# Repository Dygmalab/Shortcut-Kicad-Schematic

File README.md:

Shortcut v4 schematic and board layout. This is the version that
[Dygma](http://www.dygma.com) used for conducting closed beta testing of the
shortcut gaming keyboard.

[Schematic PDF](schematic.pdf)

Copyright Dygma 2017.

The firmware for the keyboard is part of the [Kaleidoscope
project](https://github.com/keyboardio/Kaleidoscope). The
specific implementation is defined in the [Shortcut Hardware
Plugin](https://github.com/Dygmalab/Kaleidoscope-Hardware-Shortcut).

This documentation describes Open Hardware and is licensed under the
[CERN OHL v. 1.2.](cern_ohl_v_1_2.txt)

You may redistribute and modify this documentation under the terms of the
CERN OHL v.1.2. (http://ohwr.org/cernohl). This documentation is distributed
WITHOUT ANY EXPRESS OR IMPLIED WARRANTY, INCLUDING OF
MERCHANTABILITY, SATISFACTORY QUALITY AND FITNESS FOR A
PARTICULAR PURPOSE. Please see the CERN OHL v.1.2 for applicable
conditions

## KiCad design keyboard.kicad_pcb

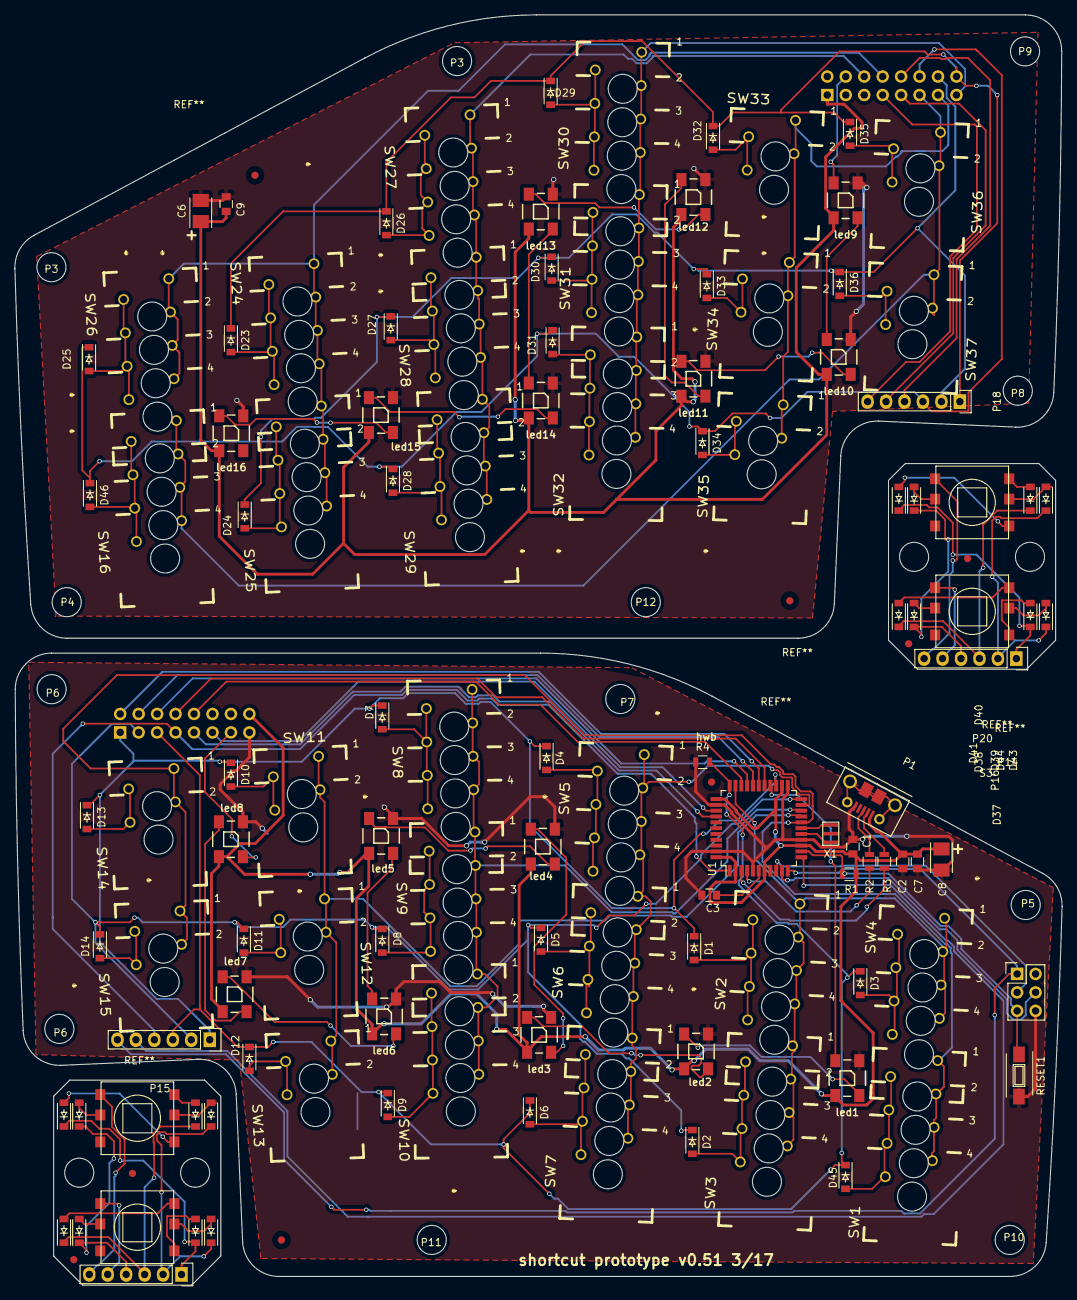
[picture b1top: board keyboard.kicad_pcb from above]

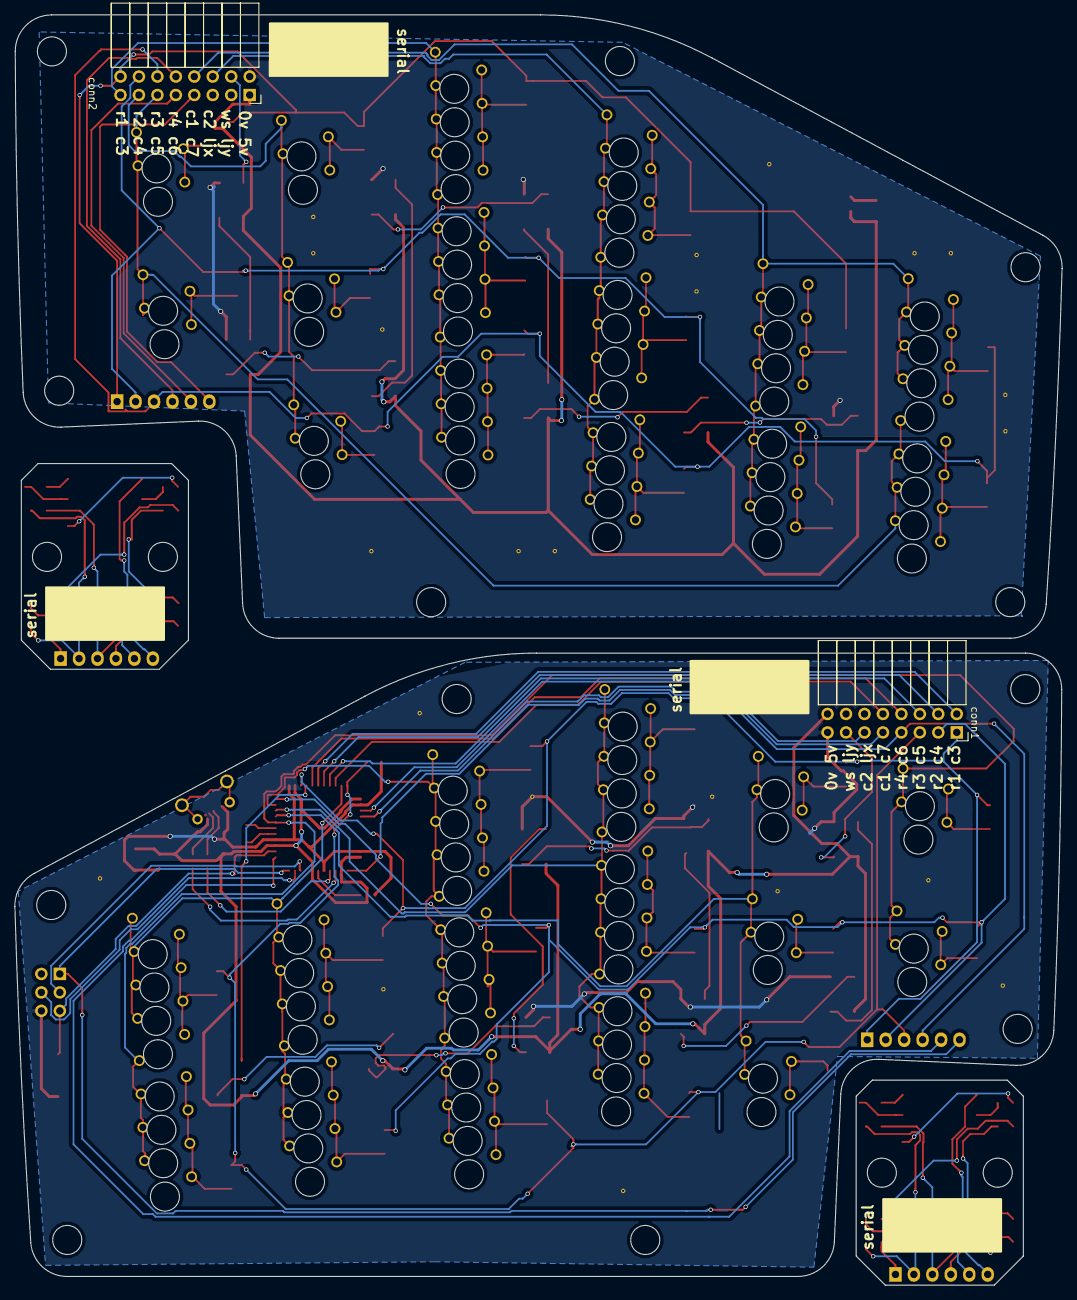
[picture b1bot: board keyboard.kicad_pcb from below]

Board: 2 copper layers, 144.1 x 174.8 mm, 134 parts (2 on the bottom side), 102 nets.

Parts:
C1, C3: 1u; C_0805
C2, C7, C9: 0.1u; C_0805
C6, C8: 2.2u; TantalC_SizeB_EIA-3528_Reflow
D1, D2, D3, D4, D5, D6, D7, D8, D9, D10, D11, D12, D13, D14, D15, D16, D17, D18, D19, D20, D21, D22, D23, D24, D25, D26, D27, D28, D29, D30, D31, D32, D33, D34, D35, D36, D37, D38, D39, D40, D41, D42, D43, D44, D45, D46: D; SOD-123
P1: USB_OTG; USB MICRO B
P2: CONN_02X03; Pin_Header_Straight_2x03
P3, P3#2, P4, P5, P6, P6#2, P7, P8, P9, P10, P11, P12, P13, P14, P17, P20: CONN_01X01; MountingHole_4mm
P15, P16, P16#2, P18: CONN_01X06; Pin_Header_Straight_1x06
R1, R4: 10k; R_0805
R2, R3: 22r; R_0805
RESET1: SW_PUSH; SW_SPST_FSMSM
S1, S2, S3, S4: alps_4way; alps 4way smt
SW1, SW2, SW3, SW4, SW5, SW6, SW7, SW8, SW9, SW10, SW16, SW24, SW25, SW26, SW27, SW28, SW29, SW30, SW31, SW32: SW_PUSH; CHERRY_MXx4
SW11, SW12, SW13, SW14, SW15, SW33, SW34, SW35, SW36, SW37: SW_PUSH; CHERRY_MXx2
U1: ATmega32U4; LQFP-44_10x10mm_Pitch0.8mm
X1: CRYSTAL_SMD; cstce-v
conn1, conn2: CONN_02X08; Socket_Strip_Angled_2x08
led1, led2, led3, led4, led5, led6, led7, led8, led9, led10, led11, led12, led13, led14, led15, led16: ws2812b; WS2812B

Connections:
+5V: C1.1, C2.1, C6.1, C7.1, C8.1, C9.1, P1.1, R1.2, U1.2, U1.7, U1.14, U1.24, U1.34, U1.44, conn1.16, conn2.1, led1.1, led2.1, led3.1, led4.1, led5.1, led6.1, led7.1, led8.1, led9.1, led10.1, led11.1, led12.1, led13.1, led14.1, led15.1, led16.1
/col1: U1.37, conn1.9
/col2: U1.36, conn1.11
/col3: U1.28, conn1.2
/col4: U1.29, conn1.4
/col5: U1.30, conn1.6
/col6: U1.27, conn1.8
/col7: U1.31, conn1.10
/col8: SW2.1, SW3.1, SW4.1, U1.32
/col9: SW5.1, SW6.1, SW7.1, U1.21
/col10: SW8.1, SW9.1, SW10.1, U1.20
/col11: SW11.1, SW12.1, SW13.1, U1.19
/col12: SW1.1, SW14.1, SW15.1, U1.18
/col13: P15.5, U1.12
/col14: P2.1, P15.6, U1.11
/l-col1: SW24.1, SW25.1, SW26.1, conn2.8
/l-col2: SW27.1, SW28.1, SW29.1, conn2.6
/l-col3: SW30.1, SW31.1, SW32.1, conn2.15
/l-col4: SW33.1, SW34.1, SW35.1, conn2.13
/l-col5: SW16.1, SW36.1, SW37.1, conn2.11
/l-col6: P18.5, conn2.9
/l-col7: P18.6, conn2.7
/l-row1: D23.1, D26.1, D29.1, D32.1, D35.1, P18.1, conn2.16
/l-row2: D24.1, D27.1, D30.1, D33.1, D36.1, P18.2, conn2.14
/l-row3: D25.1, D28.1, D31.1, D34.1, D46.1, P18.3, conn2.12
/l-row4: P18.4, conn2.10
/l-ws2812-out: conn2.4, led9.4
/mosi: P2.4, U1.10
/reset: P2.5, R1.1, RESET1.1, U1.13
/right keys/thumb/col1: P16.5, P16#2.5, S1.4, S3.4
/right keys/thumb/col2: P16.6, P16#2.6, S2.4, S4.4
/right keys/thumb/row1: D15.1, D19.1, D37.1, D41.1, P16.1, P16#2.1
/right keys/thumb/row2: D16.1, D20.1, D38.1, D42.1, P16.2, P16#2.2
/right keys/thumb/row3: D17.1, D21.1, D39.1, D43.1, P16.3, P16#2.3
/right keys/thumb/row4: D18.1, D22.1, D40.1, D44.1, P16.4, P16#2.4
/row1: D1.1, D4.1, D7.1, D10.1, D13.1, P15.1, U1.25, conn1.1
/row2: D2.1, D5.1, D8.1, D11.1, D14.1, P15.2, U1.22, conn1.3
/row3: D3.1, D6.1, D9.1, D12.1, D45.1, P15.3, R4.2, U1.33, conn1.5
/row4: P15.4, U1.1, conn1.7
/sck: P2.3, U1.9
/ws2812: U1.26, led1.4
/ws2812-out: conn1.13, led8.2
Earth: C1.2, C2.2, C3.2, C6.2, C7.2, C8.2, C9.2, P1.5, P2.6, R4.1, RESET1.2, U1.5, U1.15, U1.23, U1.35, U1.43, X1.3, conn1.15, conn2.2, led1.3, led2.3, led3.3, led4.3, led5.3, led6.3, led7.3, led8.3, led9.3, led10.3, led11.3, led12.3, led13.3, led14.3, led15.3, led16.3
unnamed: C3.1, U1.6
unnamed: D1.2, SW2.2
unnamed: D2.2, SW3.2
unnamed: D3.2, SW4.2
unnamed: D4.2, SW5.2
unnamed: D5.2, SW6.2
unnamed: D6.2, SW7.2
unnamed: D7.2, SW8.2
unnamed: D8.2, SW9.2
unnamed: D9.2, SW10.2
unnamed: D10.2, SW11.2
unnamed: D11.2, SW12.2
unnamed: D12.2, SW13.2
unnamed: D13.2, SW14.2
unnamed: D14.2, SW15.2
unnamed: D15.2, D37.2, S1.1, S3.1
unnamed: D16.2, D38.2, S1.2, S3.2
unnamed: D17.2, D39.2, S1.3, S3.3
unnamed: D18.2, D40.2, S1.5, S3.5
unnamed: D19.2, D41.2, S2.1, S4.1
unnamed: D20.2, D42.2, S2.2, S4.2
unnamed: D21.2, D43.2, S2.3, S4.3
unnamed: D22.2, D44.2, S2.5, S4.5
unnamed: D23.2, SW24.2
unnamed: D24.2, SW25.2
unnamed: D25.2, SW26.2
unnamed: D26.2, SW27.2
unnamed: D27.2, SW28.2
unnamed: D28.2, SW29.2
unnamed: D29.2, SW30.2
unnamed: D30.2, SW31.2
unnamed: D31.2, SW32.2
unnamed: D32.2, SW33.2
unnamed: D33.2, SW34.2
unnamed: D34.2, SW35.2
unnamed: D35.2, SW36.2
unnamed: D36.2, SW37.2
unnamed: D45.2, SW1.2
unnamed: D46.2, SW16.2
unnamed: P1.2, R3.2
unnamed: P1.3, R2.2
unnamed: R2.1, U1.4
unnamed: R3.1, U1.3
unnamed: U1.16, X1.2
unnamed: U1.17, X1.1
unnamed: led1.2, led2.4
unnamed: led2.2, led3.4
unnamed: led3.2, led4.4
unnamed: led4.2, led5.4
unnamed: led5.2, led6.4
unnamed: led6.2, led7.4
unnamed: led7.2, led8.4
unnamed: led10.2, led11.4
unnamed: led9.2, led10.4
unnamed: led11.2, led12.4
unnamed: led12.2, led13.4
unnamed: led13.2, led14.4
unnamed: led14.2, led15.4
unnamed: led15.2, led16.4

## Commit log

2016-12-06 mid sheet organise
2016-12-06 finished schematic
2016-12-07 added wire interconnects between sockets
2016-12-07 right hand side initial layout
2016-12-07 picoflex connectors & good idea of board layout
2016-12-12 libs and thumboard components done
2016-12-13 smt 4 ways
2016-12-15 removed joysticks, changed board conns, changed thumb conns
2016-12-15 buttons shifted
2016-12-15 nearly routed
2016-12-16 final checks, silks, labels, ground pours, layout
2016-12-16 sent to fab
2017-01-13 part numbers for 4 ways and reset switch
2017-02-21 v5 switches routed + outline
2017-02-22 v5 prefab
2017-02-24 fix non smt components
2017-02-28 fixed: silks, fids, col2 via, serial patches
2017-02-28 removed silk cross
2017-02-28 added hwb resistor
2017-02-28 redid thumboard components
2017-03-02 shortened thumbs, fid refs
2017-03-02 fix vias under pads, serial silks
2017-03-03 2 and 4 position cherry keys
2017-03-07 changed size to a3 and moved boards
2017-03-13 moved outlines
2017-11-03 license and readme
2017-11-03 libraries and footprints
2017-11-03 schematic and board layout
2017-11-03 added links to firmware
